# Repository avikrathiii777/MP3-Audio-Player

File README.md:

# ESP32 Bluetooth MP3 Player

This is a pocket-sized Bluetooth MP3 player that stands on its own. It is built around a custom **ESP32-WROOM-32E** PCB and a custom two-piece **3D-printed resin enclosure**. The player reads `.mp3` tracks from a MicroSD card. It decodes stereo audio in time. Then it sends the sound wirelessly through Bluetooth A2DP to headphones (**JBL Tune 770NC**). You control playback and volume with buttons. Anyways I haven't built it as of yet. Here are a the images of the PCB and the schematic with a 3D view from KiCad-

---

## Features & Hardware Architecture

* **Microcontroller & Bluetooth Audio:** The `ESP32-WROOM-32E` streams audio over Bluetooth Classic (`A2DP Source`).

* **Storage:** A push-pull MicroSD card slot (`Hirose DM3D-SF`) is wired over hardware `VSPI`.

* **Power & USB-C Charging:**

* The `USB-C` receptacle (`, 16-pin) uses `5.1kΩ` `CC1`/`CC2` resistors so it works with standard 5V USB-C chargers.

* A `TP4056` linear Li-Ion charger IC is set for `1A` charging (``PROG` resistor).

* An `AP2112K-3.3` `600mA` low-dropout voltage regulator gives 3.3V` power from a `3.7V` LiPo battery.

* A physical `SPDT` slide switch (`SW2`) cuts the power at the hardware level.

* **Physical Controls:** There are 6 push buttons (`Play`, `Pause`, `Next`, `Previous`, `Volume Up`, `Volume Down`). There is also a BOOT` button (`SW1`) and a 4-pin UART programming header (`J3`).

* **Custom 2-Piece Enclosure:** I designed it in FreeCAD with cutouts for USB-C, MicroSD, the slide switch and all 6 buttons. The ESP32 PCB antenna stays clear under resin.

---

## Hardware & CAD Previews

| 3D Enclosure Assembly | JLCPCB Cart (PCB + 3D Case) |
| :---: | :---: |
|  |  |

---

## GPIO Pinout

| Function | ESP32 GPIO | Notes |

| :--- | :--- | :---

| **MicroSD `CS`** | `GPIO 5` | VSPI Chip Select |

| **MicroSD `SCK`** | `GPIO 18` | VSPI Clock |

| **MicroSD `MISO`** | `GPIO 19` | VSPI Data Out |

| **MicroSD `MOSI`** | `GPIO 23` | VSPI Data In

| **Play** | `GPIO 13` | Active-Low (`INPUT_PULLUP`) |

| **Pause** | `GPIO 14` | Active-Low (`INPUT_PULLUP`) |

| **Next Track** | `GPIO 16` | Active-Low (`INPUT_PULLUP`) |

| **Previous Track** | `GPIO 17` | Active-Low (`INPUT_PULLUP`) |

| **Volume Up** | `GPIO 25` | Active-Low (`INPUT_PULLUP`) |

| **Volume Down** | `GPIO 27` | Active-Low (`INPUT_PULLUP`) |

---

## Bill of Materials (BOM)

| Qty | Reference | Component | Package / Spec | Supplier | Est. Cost |
| :--- | :--- | :--- | :--- | :--- | :--- |
| **5** | `PCB` | Custom 2-Layer PCB (`72 × 55 mm`) | `1.6 mm` FR-4, Green | JLCPCB | \$4.00 |
| **1** | `CASE` | 3D Printed Upper & Lower Case | `9600` White Resin (SLA) | JLCPCB 3DP | \$2.38 |
| — | `SHIPPING` | JLCPCB Combined Shipping (after coupon) | International Shipping | JLCPCB | -\$0.46 *(Net \$5.92 total)* |
| **1** | `U1` | `ESP32-WROOM-32E` | SMD Module | Robu.in / Evelta | ₹260 (~\$3.05) |
| **1** | `U2` | `TP4056` LiPo Charger IC | `ESOP-8` | Robu.in / ElectronicsComp | ₹15 (~\$0.18) |
| **1** | `U3` | `AP2112K-3.3` 3.3V LDO Regulator | `SOT-23-5` | Evelta / LCSC | ₹20 (~\$0.24) |
| **1** | `J2` | USB-C 16-Pin Receptacle (`USB4105`) | SMD Horizontal | Robu.in / Evelta | ₹35 (~\$0.41) |
| **1** | `J1` | MicroSD Push-Pull Socket (`DM3D-SF`) | SMD | Evelta / LCSC | ₹45 (~\$0.53) |
| **7** | `SW1`, `Play1`, `Pause1`, `Next1`, `Previous1`, `volUp1`, `volDown1` | Tactile Push Button Switch | `6 × 6 mm` Through-Hole | Robu.in / ElectronicsComp | ₹20 (~\$0.24) |
| **1** | `SW2` | SPDT Slide Switch (`PCM12`) | 3-Pin SMD | Robu.in / Evelta | ₹15 (~\$0.18) |
| **4** | `C1, C2, C3, C4` | `10µF` Ceramic Capacitor | `0805` SMD | Robu.in / Evelta | ₹10 (~\$0.12) |
| **2** | `R1, R2` | `10kΩ` Resistor (`EN` & `BOOT`) | `0805` SMD | Robu.in / Evelta | ₹5 (~\$0.06) |
| **2** | `R3, R4` | `5.1kΩ` Resistor (`USB-C CC1/CC2`) | `0805` SMD | Robu.in / Evelta | ₹5 (~\$0.06) |
| **1** | `R5` | `1.2kΩ` Resistor (`TP4056 PROG`) | `0805` SMD | Robu.in / Evelta | ₹5 (~\$0.06) |
| **2** | `J3, J4` | `1×4` UART Header & `1×2` Battery Header | `2.54 mm` Pitch | Robu.in / ElectronicsComp | ₹10 (~\$0.12) |
| **1** | `BAT1` | `3.7V` LiPo Rechargeable Battery | `600mAh` Pouch Cell | Robu.in / ElectronicsComp | ₹250 (~\$2.95) |

**Estimated Grand Total:** **~\$14.12 USD (~₹1,200 INR)** including custom PCBs, resin 3D-printed enclosure, shipping, and all electronic components.

---

## Firmware Setup & Compilation

1. **Board Package:** Install **`by Espressif Systems (`v3.0.7`)** in the Arduino IDE.

2. **Required Libraries** (install via *Sketch > Include Library > Add.ZIP Library...*):

* [`ESP32-A2DP`](https://github.com)

* [`arduino-audio-tools` (`v1.0.1`)](https://github.com)

* [`arduino-libhelix`](https://github.com)

3. **Arduino IDE Settings:**

* **Board:** `ESP32 Dev Module`

* **Partition Scheme:** `Huge APP (3MB No OTA/1MB SPIFFS)`

4. **Usage:** Put `.mp3` files in the root directory of a FAT32-formatted MicroSD card. Change `BT_DEVICE_NAME` in `Firmware/firmware.ino` if you use headphones. Then flash the board through the 4-pin UART header (`3V3`, `GND`, `TX`, `RX`).

---

## Third-Party Libraries & Licensing

This project leans on open-source ESP32 audio and Bluetooth libraries:

* **[ESP32-A2DP](https://github.com)** by Phil Schatzmann is licensed under the **Apache License 2.0**.

* **[arduino-audio-tools](https://github.com)** by Phil Schatzmann is licensed under the **GNU General Public License v3.0 (GPL-3.0)**.

* **[arduino-libhelix](https://github.com)** by Phil Schatzmann (a wrapper around RealNetworks Helix MP3 decoder) is licensed under the **RealNetworks Public Source License (RPSL) / GPL- terms**.

* **[Arduino-ESP32 Core](https://github.com)** by Espressif Systems is licensed under the **GNU Lesser General Public License v2.1 (LGPL-2.1)**.

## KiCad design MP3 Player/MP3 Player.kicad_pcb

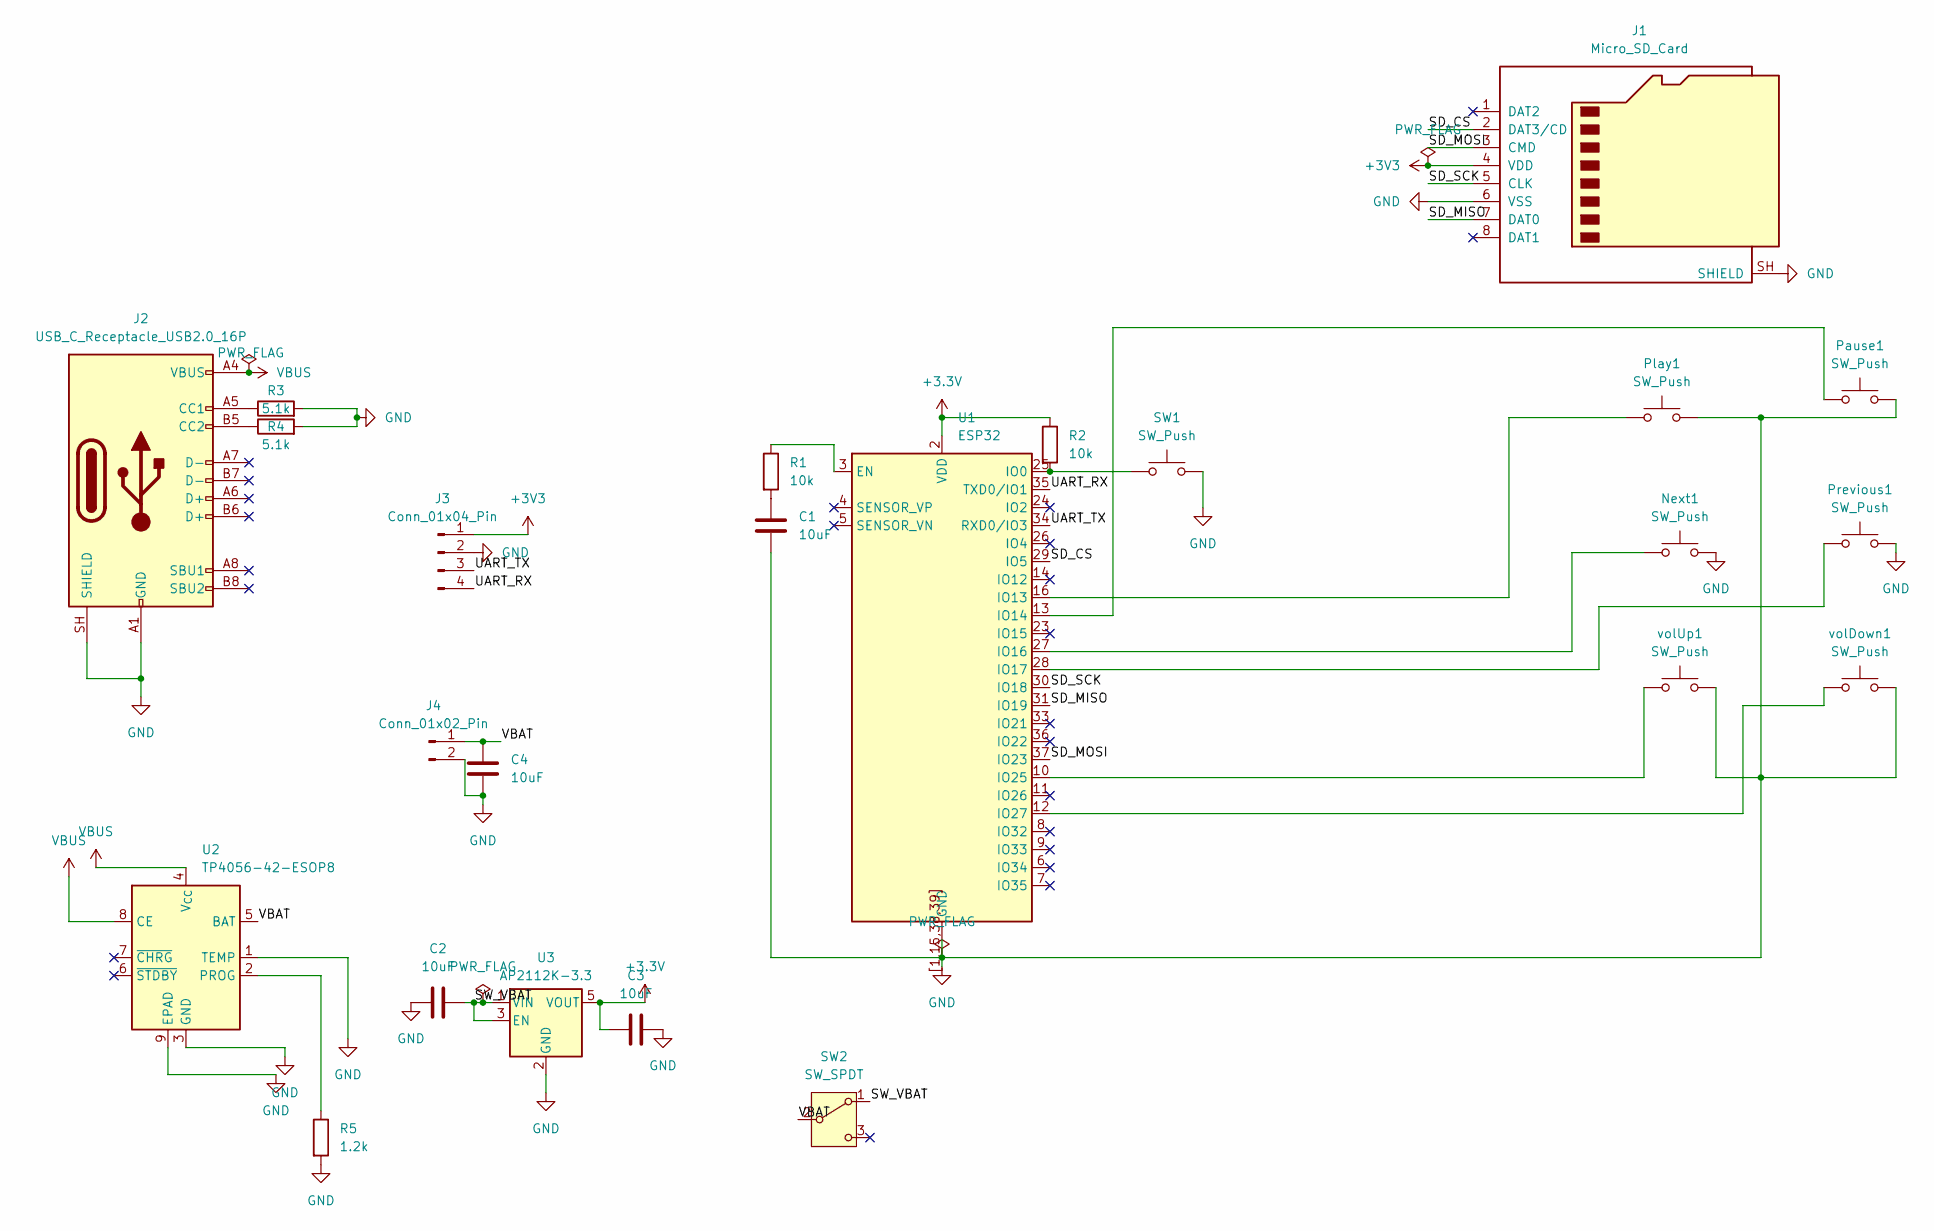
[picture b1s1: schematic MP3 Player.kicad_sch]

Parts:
C1, C2, C3, C4: 10uF; C_0805_2012Metric
J1: Micro_SD_Card; microSD_HC_Hirose_DM3D-SF
J2: USB_C_Receptacle_USB2.0_16P; USB_C_Receptacle_GCT_USB4105-xx-A_16P_TopMnt_Horizontal
J3: Conn_01x04_Pin; PinHeader_1x04_P2.54mm_Vertical
J4: Conn_01x02_Pin; PinHeader_1x02_P2.54mm_Vertical
Next1: SW_Push; SW_PUSH_6mm
Pause1: SW_Push; SW_PUSH_6mm
Play1: SW_Push; SW_PUSH_6mm
Previous1: SW_Push; SW_PUSH_6mm
R1, R2: 10k; R_0805_2012Metric
R3, R4: 5.1k; R_0805_2012Metric
R5: 1.2k; R_0805_2012Metric
SW1: SW_Push; R_0805_2012Metric
SW2: SW_SPDT; SW_SPDT_PCM12
U1: ESP32; ESP32-WROOM-32E
U2: TP4056-42-ESOP8; SOIC-8-1EP_3.9x4.9mm_P1.27mm_EP2.41x3.3mm_ThermalVias
U3: AP2112K-3.3; SOT-23-5
volDown1: SW_Push; SW_PUSH_6mm
volUp1: SW_Push; SW_PUSH_6mm

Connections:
+3.3V: C3.1, R2.1, U1.2 (VDD), U3.5 (VOUT)
+3V3: J1.4 (VDD), J3.1
/SD_CS: J1.2 (DAT3/CD), U1.29 (IO5)
/SD_MISO: J1.7 (DAT0), U1.31 (IO19)
/SD_MOSI: J1.3 (CMD), U1.37 (IO23)
/SD_SCK: J1.5 (CLK), U1.30 (IO18)
/SW_VBAT: C2.2, SW2.1 (A), U3.1 (VIN), U3.3 (EN)
/UART_RX: J3.4, U1.35 (TXD0/IO1)
/UART_TX: J3.3, U1.34 (RXD0/IO3)
/VBAT: C4.1, J4.1, SW2.2 (B), U2.5 (BAT)
GND: C1.2, C2.1, C3.2, C4.2, J1.6 (VSS), J1.SH (SHIELD), J2.A1 (GND), J2.A12 (GND), J2.B1 (GND), J2.B12 (GND), J2.SH (SHIELD), J3.2, J4.2, Next1.2, Pause1.2, Play1.2, Previous1.2, R3.2, R4.2, R5.2, SW1.2, U1.1 (GND), U1.15 (GND), U1.38 (GND), U1.39 (GND), U1.[1,15,38,39] (GND), U2.1 (TEMP), U2.3 (GND), U2.9 (EPAD), U3.2 (GND), volDown1.2, volUp1.2
unnamed: C1.1, R1.2
unnamed: J2.A5 (CC1), R3.1
unnamed: J2.B5 (CC2), R4.1
unnamed: R1.1, U1.3 (EN)
unnamed: R2.2, SW1.1, U1.25 (IO0)
unnamed: Play1.1, U1.16 (IO13)
unnamed: Pause1.1, U1.13 (IO14)
unnamed: Next1.1, U1.27 (IO16)
unnamed: Previous1.1, U1.28 (IO17)
unnamed: U1.10 (IO25), volUp1.1
unnamed: U1.12 (IO27), volDown1.1
unnamed: R5.1, U2.2 (PROG)
VBUS: J2.A4 (VBUS), J2.A9 (VBUS), J2.B4 (VBUS), J2.B9 (VBUS), U2.4 (V_{CC}), U2.8 (CE)

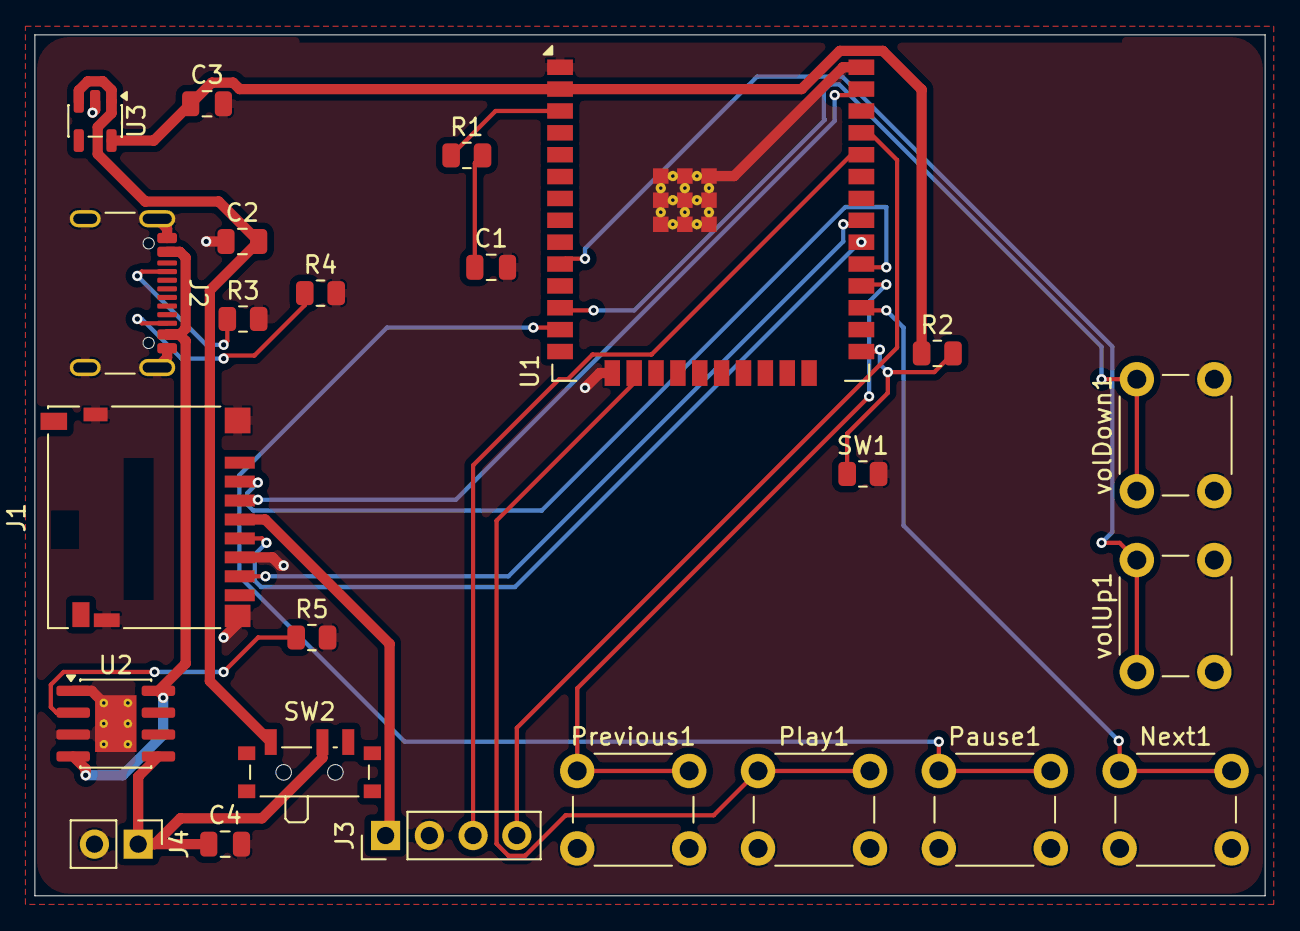
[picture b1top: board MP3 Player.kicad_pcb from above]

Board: 2 copper layers, 71.5 x 50.0 mm, 24 parts (0 on the bottom side), 24 nets.

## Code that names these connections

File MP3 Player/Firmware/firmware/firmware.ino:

#include <SPI.h>
#include <SD.h>
#include <vector>
#include "AudioTools.h"
#include "AudioTools/AudioLibs/A2DPStream.h"
#include "AudioTools/AudioCodecs/CodecMP3Helix.h"

#define SD_CS 5
#define SD_SCK 18
#define SD_MISO 19
#define SD_MOSI 23
#define BTN_PLAY 13
#define BTN_PAUSE 14
#define BTN_NEXT 16
#define BTN_PREV 17
#define BTN_VOLUP 25
#define BTN_VOLDN 27

const char* BT_DEVICE_NAME = "JBL Tune 770NC";

A2DPStream out;
MP3DecoderHelix mp3;
EncodedAudioStream decoder(&out, &mp3);
StreamCopy copier;
File currentFile;
std::vector<String> playlist;
int currentTrack = 0;
bool isPlaying = false;
int volumeLevel = 70;
unsigned long lastButtonTime = 0;

void loadPlaylist(File dir) {
  while(true) {
    File entry = dir.openNextFile();
    if (!entry) break;
    if (!entry.isDirectory()) {
      String name = String(entry.name());
      if (!name.startsWith("/")) name = "/" + name;
      String lower = name;
      lower.toLowerCase();
      if (lower.endsWith(".mp3") && !lower.startsWith("/.")) {
        playlist.push_back(name);
        Serial.println("Added track: " + name);
      }
    }
    entry.close();
  }
}

void playTrack(int index) {
  if (playlist.empty()) return;
  if (index < 0) index = playlist.size() - 1;
  if (index >= (int)playlist.size()) index = 0;
  currentTrack = index;

  if(currentFile) currentFile.close();
  currentFile = SD.open(playlist[currentTrack]);
  if (currentFile) {
    Serial.println("Now playing: " + playlist[currentTrack]);
    decoder.begin();
    copier.begin(decoder, currentFile);
    isPlaying = true;
  }
}

void setup() {
  Serial.begin(115200);
  pinMode(BTN_PLAY, INPUT_PULLUP);
  pinMode(BTN_PAUSE, INPUT_PULLUP);
  pinMode(BTN_NEXT, INPUT_PULLUP);
  pinMode(BTN_PREV, INPUT_PULLUP);
  pinMode(BTN_VOLUP, INPUT_PULLUP);
  pinMode(BTN_VOLDN, INPUT_PULLUP);

  SPI.begin(SD_SCK, SD_MISO, SD_MOSI, SD_CS);
  if (!SD.begin(SD_CS)) {
    Serial.println("SD Card Mount Failed");
    while (true) delay(1000);
  }

  File root = SD.open("/");
  loadPlaylist(root);
  root.close();

  Serial.println("Connecting to bluetooth device.....");
  auto cfg = out.defaultConfig(TX_MODE);
  cfg.name = BT_DEVICE_NAME;
  cfg.auto_reconnect = true;
  out.begin(cfg);
  out.setVolume(volumeLevel / 100.0);

  if (!playlist.empty()) {
    playTrack(0);
  }
}

void handleButtons() {
  if (millis() - lastButtonTime < 220) return;

  if (digitalRead(BTN_PLAY) == LOW) {
    lastButtonTime = millis();
    if (!isPlaying) {
      if (!currentFile) playTrack(currentTrack);
      else isPlaying = true;
      Serial.println("Resumed");
    }
  }
  else if (digitalRead(BTN_PAUSE) == LOW) {
    lastButtonTime = millis();
    isPlaying = false;
    Serial.println("Paused");
  }
  else if (digitalRead(BTN_NEXT) == LOW) {
    lastButtonTime = millis();
    playTrack(currentTrack + 1);
  }
  else if (digitalRead(BTN_PREV) == LOW) {
    lastButtonTime = millis();
    playTrack(currentTrack - 1);
  }
  else if (digitalRead(BTN_VOLUP) == LOW) {
    lastButtonTime = millis();
    volumeLevel = min(100, volumeLevel + 10);
    out.source().set_volume(volumeLevel);
    Serial.printf("Volume: %d%%\n", volumeLevel);
  }
  else if (digitalRead(BTN_VOLDN) == LOW) {
    lastButtonTime = millis();
    volumeLevel = max(0, volumeLevel - 10);
    out.source().set_volume(volumeLevel);
    Serial.printf("Volume: %d%%\n", volumeLevel);
  }
}

void loop() {
  handleButtons();
  if (isPlaying && currentFile) {
    if (!copier.copy()) {
      playTrack(currentTrack + 1);      
    }
  } else {
    delay(10);
  }
}
